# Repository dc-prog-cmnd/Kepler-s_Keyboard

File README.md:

# Kepler's keyboard: A custom 75% Keyboard.
I started this a while ago, and I learned a lot of new things about electronics and design as a result. It was one of the most frustrating things I have ever done, but I think that the final product will turn out well (fingers crossed)

I finished the case, and I think that I'll make it out of wood. My school has got some saws for me to work with, and I think it'll be a fun challenge. I chose a sandwich mount because this is my first keyboard I designed, and it wasn't as difficult to design as the others. 

# Schematic

The build uses a nice!nano, similar to many other custom builds. I went with an encoder to make a little bit more unique. 

# PCB

This is the 4th or 5th iteration of the PCB because of problems I encountered with wiring the keys. I based the design on the Keycool 84. 

# TOP Plate

I'm using a sandwich mount for the keyboard, so this PCB will be my plate.

# Firmware 
A.I. and the ZMK guide helped me here because ZMK was troubling to figure out, but I eventually got it.

(more information about the build process is available in the journal)

# Bill of Materials (BOM) 
(4) 25 mm M2 screws
(1) Nice!nano Microcontroller 
(88) 1N4148W switching diodes 
(84) Cherry MX Red Switches
(84) Blank White DSA Keycaps
(1) Push-button THT Switch 
(1) Alps EC11E Rotary Encoder 
(1) Lithium Battery 110mAh: 
(4) Brass set heat inserts

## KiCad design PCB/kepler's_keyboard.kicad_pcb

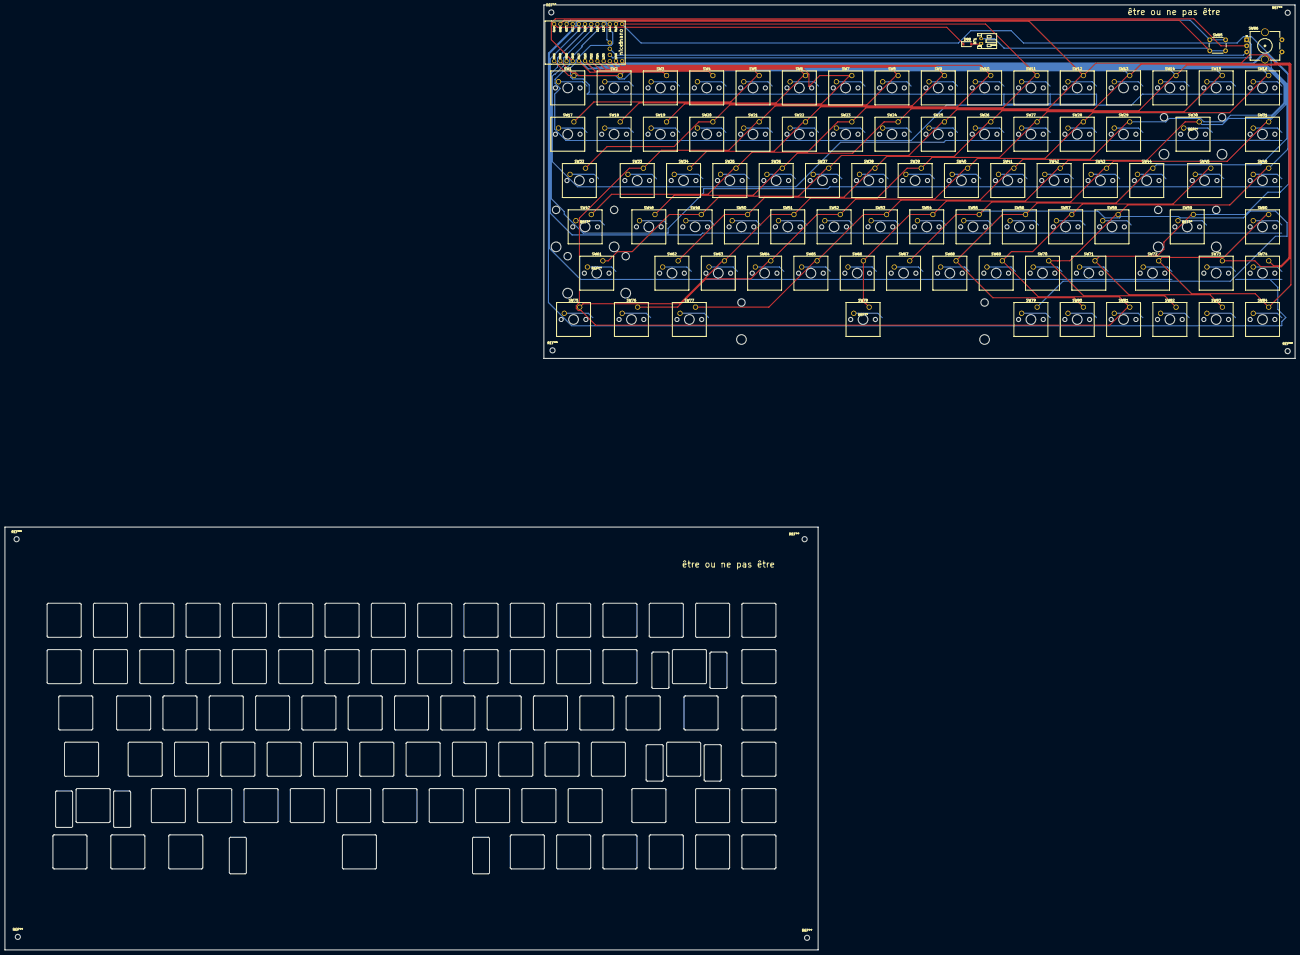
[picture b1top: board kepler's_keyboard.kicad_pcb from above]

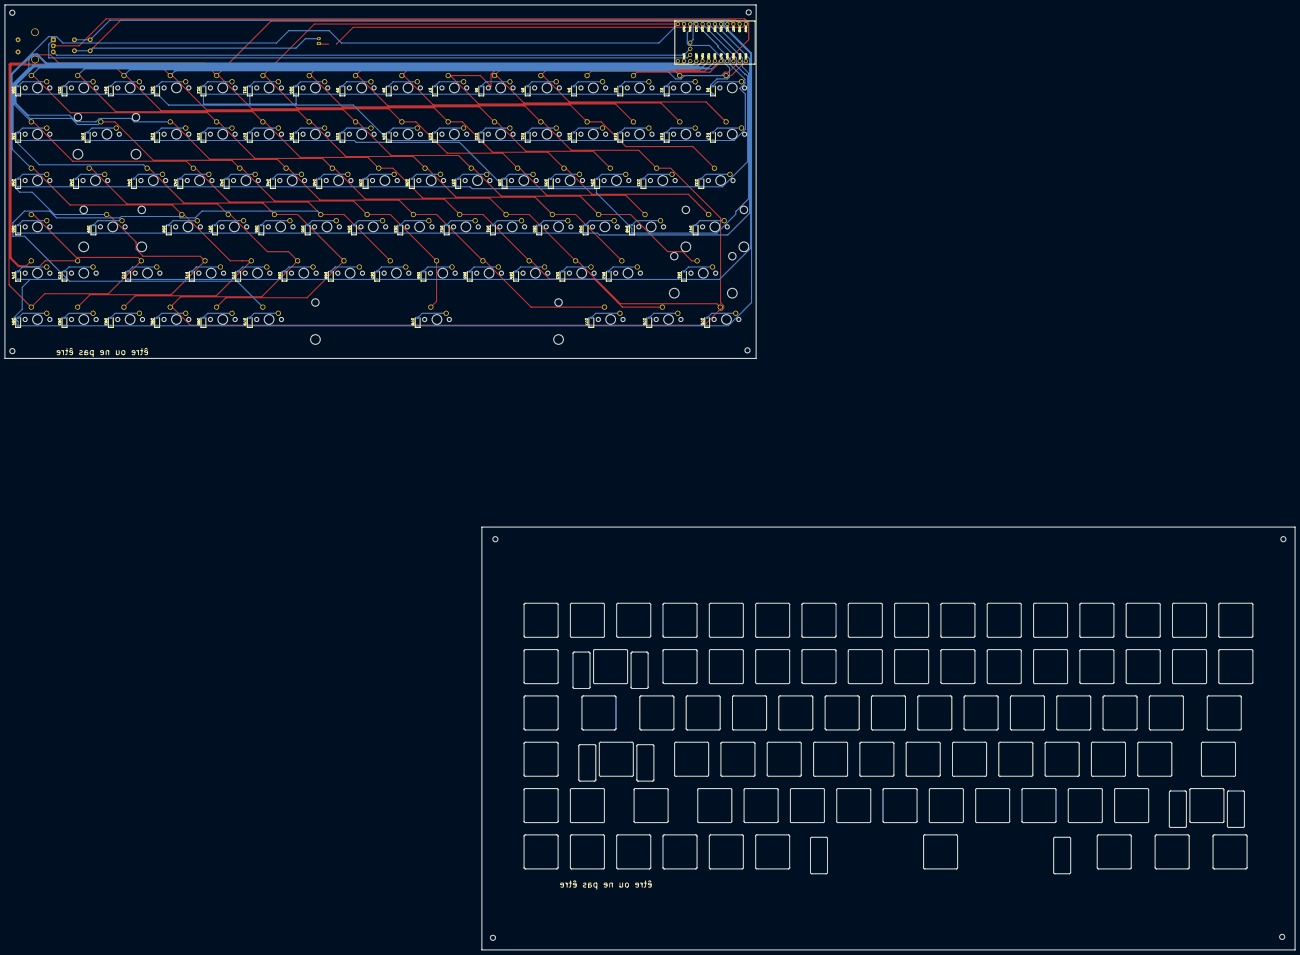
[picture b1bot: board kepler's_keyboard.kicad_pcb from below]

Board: 2 copper layers, 309.0 x 145.4 mm, 173 parts (84 on the bottom side), 110 nets.

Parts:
BT1: Battery_Cell; JST_PH_S2B-PH-K_1x02_P2.00mm_Horizontal
D1, D2, D3, D4, D5, D6, D7, D8, D9, D10, D11, D12, D13, D14, D15, D16, D17, D18, D19, D20, D21, D22, D23, D24, D25, D26, D27, D28, D29, D30, D31, D32, D33, D34, D35, D36, D37, D38, D39, D40, D41, D42, D43, D44, D45, D46, D47, D48, D49, D50, D51, D52, D53, D54, D55, D56, D57, D58, D59, D60, D61, D62, D63, D64, D65, D66, D67, D68, D69, D70, D71, D72, D73, D74, D75, D76, D77, D78, D79, D80, D81, D82, D83, D84, D88: D; D_SOD-123
SW1, SW2, SW3, SW4, SW5, SW6, SW7, SW8, SW9, SW10, SW11, SW12, SW13, SW14, SW15, SW16, SW17, SW18, SW19, SW20, SW21, SW22, SW23, SW24, SW25, SW26, SW27, SW28, SW29, SW30, SW31, SW32, SW33, SW34, SW35, SW36, SW37, SW38, SW39, SW40, SW41, SW42, SW43, SW44, SW45, SW46, SW47, SW48, SW49, SW50, SW51, SW52, SW53, SW54, SW55, SW56, SW57, SW58, SW59, SW60, SW61, SW62, SW63, SW64, SW65, SW66, SW67, SW68, SW69, SW70, SW71, SW72, SW73, SW74, SW75, SW76, SW77, SW78, SW79, SW80, SW81, SW82, SW83, SW84: SW_Push_45deg; SW_Cherry_MX_1.00u_PCB
SW85: SW_Push; SW_PUSH_6mm
SW86: RotaryEncoder; RotaryEncoder_Alps_EC11E-Switch_Vertical_H20mm_CircularMoun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
U1: nice_nano

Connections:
unnamed: BT1.1 (+), D88.2 (A)
unnamed: BT1.2 (-), SW85.2, U1.23 (GND)
unnamed: D1.2 (A), SW1.2
unnamed: D2.2 (A), SW2.2
unnamed: D3.2 (A), SW3.2
unnamed: D4.2 (A), SW4.2
unnamed: D5.2 (A), SW5.2
unnamed: D6.2 (A), SW6.2
unnamed: D7.2 (A), SW7.2
unnamed: D8.2 (A), SW8.2
unnamed: D9.2 (A), SW9.2
unnamed: D10.2 (A), SW10.2
unnamed: D11.2 (A), SW11.2
unnamed: D12.2 (A), SW12.2
unnamed: D13.2 (A), SW13.2
unnamed: D14.2 (A), SW14.2
unnamed: D15.2 (A), SW15.2
unnamed: D16.2 (A), SW16.2
unnamed: D17.2 (A), SW17.2
unnamed: D18.2 (A), SW18.2
unnamed: D19.2 (A), SW19.2
unnamed: D20.2 (A), SW20.2
unnamed: D21.2 (A), SW21.2
unnamed: D22.2 (A), SW22.2
unnamed: D23.2 (A), SW23.2
unnamed: D24.2 (A), SW24.2
unnamed: D25.2 (A), SW25.2
unnamed: D26.2 (A), SW26.2
unnamed: D27.2 (A), SW27.2
unnamed: D28.2 (A), SW28.2
unnamed: D29.2 (A), SW29.2
unnamed: D30.2 (A), SW30.2
unnamed: D31.2 (A), SW31.2
unnamed: D32.2 (A), SW32.2
unnamed: D33.2 (A), SW33.2
unnamed: D34.2 (A), SW34.2
unnamed: D35.2 (A), SW35.2
unnamed: D36.2 (A), SW36.2
unnamed: D37.2 (A), SW37.2
unnamed: D38.2 (A), SW38.2
unnamed: D39.2 (A), SW39.2
unnamed: D40.2 (A), SW40.2
unnamed: D41.2 (A), SW41.2
unnamed: D42.2 (A), SW42.2
unnamed: D43.2 (A), SW43.2
unnamed: D44.2 (A), SW44.2
unnamed: D45.2 (A), SW45.2
unnamed: D46.2 (A), SW46.2
unnamed: D47.2 (A), SW47.2
unnamed: D48.2 (A), SW48.2
unnamed: D49.2 (A), SW49.2
unnamed: D50.2 (A), SW50.2
unnamed: D51.2 (A), SW51.2
unnamed: D52.2 (A), SW52.2
unnamed: D53.2 (A), SW53.2
unnamed: D54.2 (A), SW54.2
unnamed: D55.2 (A), SW55.2
unnamed: D56.2 (A), SW56.2
unnamed: D57.2 (A), SW57.2
unnamed: D58.2 (A), SW58.2
unnamed: D59.2 (A), SW59.2
unnamed: D60.2 (A), SW60.2
unnamed: D61.2 (A), SW61.2
unnamed: D62.2 (A), SW62.2
unnamed: D63.2 (A), SW63.2
unnamed: D64.2 (A), SW64.2
unnamed: D65.2 (A), SW65.2
unnamed: D66.2 (A), SW66.2
unnamed: D67.2 (A), SW67.2
unnamed: D68.2 (A), SW68.2
unnamed: D69.2 (A), SW69.2
unnamed: D70.2 (A), SW70.2
unnamed: D71.2 (A), SW71.2
unnamed: D72.2 (A), SW72.2
unnamed: D73.2 (A), SW73.2
unnamed: D74.2 (A), SW74.2
unnamed: D75.2 (A), SW75.2
unnamed: D76.2 (A), SW76.2
unnamed: D77.2 (A), SW77.2
unnamed: D78.2 (A), SW78.2
unnamed: D79.2 (A), SW79.2
unnamed: D80.2 (A), SW80.2
unnamed: D81.2 (A), SW81.2
unnamed: D82.2 (A), SW82.2
unnamed: D83.2 (A), SW83.2
unnamed: D84.2 (A), SW84.2
unnamed: D88.1 (K), U1.24 (BATIN/P0.04)
unnamed: SW86.C, U1.4 (GND)
unnamed: SW86.A, U1.31 (P1.01)
unnamed: SW86.B, U1.32 (P1.02)
unnamed: SW85.1, U1.22 (RST)
col0: SW1.1, SW13.1, SW25.1, SW37.1, SW49.1, SW61.1, SW73.1, U1.1 (TX0/P0.06)
col1: SW2.1, SW14.1, SW26.1, SW38.1, SW50.1, SW62.1, SW74.1, U1.2 (RX1/P0.08)
col2: SW3.1, SW15.1, SW27.1, SW39.1, SW51.1, SW63.1, SW75.1, U1.5 (P0.17)
col3: SW4.1, SW16.1, SW28.1, SW40.1, SW52.1, SW64.1, SW76.1, U1.6 (P0.20)
col4: SW5.1, SW17.1, SW29.1, SW41.1, SW53.1, SW65.1, SW77.1, U1.7 (P0.22)
col5: SW6.1, SW18.1, SW30.1, SW42.1, SW54.1, SW66.1, SW78.1, U1.8 (P0.24)
col6: SW7.1, SW19.1, SW31.1, SW43.1, SW55.1, SW67.1, SW79.1, U1.9 (P1.00)
col7: SW8.1, SW20.1, SW32.1, SW44.1, SW56.1, SW68.1, SW80.1, U1.10 (P0.11)
col8: SW9.1, SW21.1, SW33.1, SW45.1, SW57.1, SW69.1, SW81.1, U1.11 (P1.04)
col9: SW10.1, SW22.1, SW34.1, SW46.1, SW58.1, SW70.1, SW82.1, U1.12 (P1.06)
col10: SW11.1, SW23.1, SW35.1, SW47.1, SW59.1, SW71.1, SW83.1, U1.13 (NFC1/P0.09)
col11: SW12.1, SW24.1, SW36.1, SW48.1, SW60.1, SW72.1, SW84.1, U1.14 (NFC2/P0.10)
row0: D1.1 (K), D2.1 (K), D3.1 (K), D4.1 (K), D5.1 (K), D6.1 (K), D7.1 (K), D8.1 (K), D9.1 (K), D10.1 (K), D11.1 (K), D12.1 (K), U1.15 (P1.11)
row1: D13.1 (K), D14.1 (K), D15.1 (K), D16.1 (K), D17.1 (K), D18.1 (K), D19.1 (K), D20.1 (K), D21.1 (K), D22.1 (K), D23.1 (K), D24.1 (K), U1.16 (P1.13)
row2: D25.1 (K), D26.1 (K), D27.1 (K), D28.1 (K), D29.1 (K), D30.1 (K), D31.1 (K), D32.1 (K), D33.1 (K), D34.1 (K), D35.1 (K), D36.1 (K), U1.17 (P1.15)
row3: D37.1 (K), D38.1 (K), D39.1 (K), D40.1 (K), D41.1 (K), D42.1 (K), D43.1 (K), D44.1 (K), D45.1 (K), D46.1 (K), D47.1 (K), D48.1 (K), U1.18 (AIN0/P0.02)
row4: D49.1 (K), D50.1 (K), D51.1 (K), D52.1 (K), D53.1 (K), D54.1 (K), D55.1 (K), D56.1 (K), D57.1 (K), D58.1 (K), D59.1 (K), D60.1 (K), U1.19 (AIN5/P0.29)
row5: D61.1 (K), D62.1 (K), D63.1 (K), D64.1 (K), D65.1 (K), D66.1 (K), D67.1 (K), D68.1 (K), D69.1 (K), D70.1 (K), D71.1 (K), D72.1 (K), U1.20 (AIN7/P0.31)
row6: D73.1 (K), D74.1 (K), D75.1 (K), D76.1 (K), D77.1 (K), D78.1 (K), D79.1 (K), D80.1 (K), D81.1 (K), D82.1 (K), D83.1 (K), D84.1 (K), U1.33 (P1.07)

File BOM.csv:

"Reference","Qty","Value","DNP","Exclude from BOM","Exclude from Board","Footprint","Datasheet"
"BT1","1","Battery_Cell","","","","Connector_JST:JST_PH_S2B-PH-K_1x02_P2.00mm_Horizontal",""
"D1,D2,D3,D4,D5,D6,D7,D8,D9,D10,D11,D12,D13,D14,D15,D16,D17,D18,D19,D20,D21,D22,D23,D24,D25,D26,D27,D28,D29,D30,D31,D32,D33,D34,D35,D36,D37,D38,D39,D40,D41,D42,D43,D44,D45,D46,D47,D48,D49,D50,D51,D52,D53,D54,D55,D56,D57,D58,D59,D60,D61,D62,D63,D64,D65,D66,D67,D68,D69,D70,D71,D72,D73,D74,D75,D76,D77,D78,D79,D80,D81,D82,D83,D84,D88","85","D","","","","Diode_SMD:D_SOD-123",""
"SW1,SW2,SW3,SW4,SW5,SW6,SW7,SW8,SW9,SW10,SW11,SW12,SW13,SW14,SW15,SW16,SW17,SW18,SW19,SW20,SW21,SW22,SW23,SW24,SW25,SW26,SW27,SW28,SW29,SW30,SW31,SW32,SW33,SW34,SW35,SW36,SW37,SW38,SW39,SW40,SW41,SW42,SW43,SW44,SW45,SW46,SW47,SW48,SW49,SW50,SW51,SW52,SW53,SW54,SW55,SW56,SW57,SW58,SW59,SW60,SW61,SW62,SW63,SW64,SW65,SW66,SW67,SW68,SW69,SW70,SW71,SW72,SW73,SW74,SW75,SW76,SW77,SW78,SW79,SW80,SW81,SW82,SW83,SW84","84","SW_Push_45deg","","","","Button_Switch_Keyboard:SW_Cherry_MX_1.00u_PCB",""
"SW85","1","SW_Push","","","","Button_Switch_THT:SW_PUSH_6mm",""
"SW86","1","RotaryEncoder","","","","Rotary_Encoder:RotaryEncoder_Alps_EC11E-Switch_Vertical_H20mm_CircularMountingHoles",""
"U1","1","nice_nano","","","","nice!nano:nice_nano",""

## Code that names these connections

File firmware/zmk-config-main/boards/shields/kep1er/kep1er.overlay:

/* Keycool 84 (Kepler) on nice!nano, pins taken from the KiCad PCB. */

#include <dt-bindings/zmk/matrix_transform.h>
#include "kep1er-layouts.dtsi"

/ {
    chosen {
        zmk,kscan = &kscan;
        zmk,physical-layout = &default_layout;
    };

    kscan: kscan {
        compatible = "zmk,kscan-gpio-matrix";
        diode-direction = "col2row";
        wakeup-source;

        col-gpios
            = <&gpio0 6 GPIO_ACTIVE_HIGH>   /* col0  TX0/P0.06 */
            , <&gpio0 8 GPIO_ACTIVE_HIGH>   /* col1  RX1/P0.08 */
            , <&gpio0 17 GPIO_ACTIVE_HIGH>   /* col2  P0.17 */
            , <&gpio0 20 GPIO_ACTIVE_HIGH>   /* col3  P0.20 */
            , <&gpio0 22 GPIO_ACTIVE_HIGH>   /* col4  P0.22 */
            , <&gpio0 24 GPIO_ACTIVE_HIGH>   /* col5  P0.24 */
            , <&gpio1 0 GPIO_ACTIVE_HIGH>   /* col6  P1.00 */
            , <&gpio0 11 GPIO_ACTIVE_HIGH>   /* col7  P0.11 */
            , <&gpio1 4 GPIO_ACTIVE_HIGH>   /* col8  P1.04 */
            , <&gpio1 6 GPIO_ACTIVE_HIGH>   /* col9  P1.06 */
            , <&gpio0 9 GPIO_ACTIVE_HIGH>   /* col10  NFC1/P0.09 */
            , <&gpio0 10 GPIO_ACTIVE_HIGH>   /* col11  NFC2/P0.10 */
            ;

        row-gpios
            = <&gpio1 11 (GPIO_ACTIVE_HIGH | GPIO_PULL_DOWN)>   /* row0  P1.11 */
            , <&gpio1 13 (GPIO_ACTIVE_HIGH | GPIO_PULL_DOWN)>   /* row1  P1.13 */
            , <&gpio1 15 (GPIO_ACTIVE_HIGH | GPIO_PULL_DOWN)>   /* row2  P1.15 */
            , <&gpio0 2 (GPIO_ACTIVE_HIGH | GPIO_PULL_DOWN)>   /* row3  P0.02 */
            , <&gpio0 29 (GPIO_ACTIVE_HIGH | GPIO_PULL_DOWN)>   /* row4  P0.29 */
            , <&gpio0 31 (GPIO_ACTIVE_HIGH | GPIO_PULL_DOWN)>   /* row5  P0.31 */
            , <&gpio1 7 (GPIO_ACTIVE_HIGH | GPIO_PULL_DOWN)>   /* row6  P1.07 (extra pad) */
            ;
    };

    default_transform: default_transform {
        compatible = "zmk,matrix-transform";
        columns = <12>;
        rows = <7>;

        map = <
            RC(0,0) RC(0,1) RC(0,2) RC(0,3) RC(0,4) RC(0,5) RC(0,6) RC(0,7) RC(0,8) RC(0,9) RC(0,10) RC(0,11)
            RC(1,0) RC(1,1) RC(1,2) RC(1,3) RC(1,4) RC(1,5) RC(1,6) RC(1,7) RC(1,8) RC(1,9) RC(1,10) RC(1,11)
            RC(2,0) RC(2,1) RC(2,2) RC(2,3) RC(2,4) RC(2,5) RC(2,6) RC(2,7) RC(2,8) RC(2,9) RC(2,10) RC(2,11)
            RC(3,0) RC(3,1) RC(3,2) RC(3,3) RC(3,4) RC(3,5) RC(3,6) RC(3,7) RC(3,8) RC(3,9) RC(3,10) RC(3,11)
            RC(4,0) RC(4,1) RC(4,2) RC(4,3) RC(4,4) RC(4,5) RC(4,6) RC(4,7) RC(4,8) RC(4,9) RC(4,10) RC(4,11)
            RC(5,0) RC(5,1) RC(5,2) RC(5,3) RC(5,4) RC(5,5) RC(5,6) RC(5,7) RC(5,8) RC(5,9) RC(5,10) RC(5,11)
            RC(6,0) RC(6,1) RC(6,2) RC(6,3) RC(6,4) RC(6,5) RC(6,6) RC(6,7) RC(6,8) RC(6,9) RC(6,10) RC(6,11)
        >;
    };

    /* Rotary encoder: A = P1.01, B = P1.02, common (C) goes to GND on the PCB. */
    encoder: encoder {
        compatible = "alps,ec11";
        a-gpios = <&gpio1 1 (GPIO_PULL_UP | GPIO_ACTIVE_LOW)>;
        b-gpios = <&gpio1 2 (GPIO_PULL_UP | GPIO_ACTIVE_LOW)>;
        steps = <80>;
        status = "okay";
    };

    sensors: sensors {
        compatible = "zmk,keymap-sensors";
        sensors = <&encoder>;
        triggers-per-rotation = <20>;
    };
};
